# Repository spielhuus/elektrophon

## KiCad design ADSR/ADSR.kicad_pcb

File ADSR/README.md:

# The Fastest Envelope in the West

The ADSR creates an envelope for describing the change of the sound over time. The envelope can be used for amplitude, 
<a href="https://spielhuus.github.io/elektrophon/images/ADSR_panel.png"></img></a>
frequencies or pitch. The output of the ADSR module can for example be patched to a VCA or VCF. The original schematic is
used by René Schmitz and Yves Usson. 
<a href="https://spielhuus.github.io/elektrophon/images/ADSR.svg"></img></a>

<a href="https://spielhuus.github.io/elektrophon/images/ADSR.png"></img></a>

## links

1) [Wikipedia: ADSR](https://en.wikipedia.org/wiki/Envelope_(music))
1) [René Schmitz: The Fastest Envelope in the West](https://www.schmitzbits.de/adsr.html)
1) [Yves Usson: ADSR](http://www.yusynth.net/Modular/EN/ADSR/index_old.html)
1) [Falstad: Circuit simulation](https://www.falstad.com/circuit/circuitjs.html?cct=$+1+0.000005+382.76258214399064+66+5+43%0A165+288+80+384+80+6+1.7128468214015743e-7%0Ag+-192+208+-192+240+0%0AR+352+48+352+0+0+0+40+15+0+0+0.5%0At+-160+144+-128+144+0+1+-12.879237515528416+-0.40832239409727095+100%0Ar+-224+144+-288+144+0+10000%0Ad+-192+208+-192+144+2+default%0Ag+384+240+384+272+0%0Aw+-224+144+-192+144+0%0Aw+-192+144+-160+144+0%0Ar+-128+128+-128+64+0+4700%0Ar+-32+112+-32+48+0+4700%0At+-64+160+-32+160+0+1+0.5774361071439447+0.6326454792662959+100%0Ar+96+160+96+96+0+4700%0At+64+176+96+176+0+1+-14.984006479709088+0.015993518948659767+100%0AR+-128+64+-128+16+0+0+40+15+0+0+0.5%0AR+-32+48+-32+0+0+0+40+15+0+0+0.5%0AR+96+96+96+48+0+0+40+15+0+0+0.5%0Ar+-64+128+-128+128+0+22000%0Ad+16+208+16+144+2+default%0Ag+16+208+16+240+0%0Ar+64+144+16+144+0+10000%0Ac+-32+144+16+144+0+1e-8+0.039215854165133346%0Ag+96+192+96+240+0%0Ac+352+272+352+240+0+1e-8+-10.000000000000005%0Ag+352+272+352+320+0%0Aw+96+160+288+176+0%0AR+-288+144+-336+144+0+2+5+5+0+0+0.4%0Aa+592+192+688+192+8+15+-15+1000000+0.4192033211698532+0.4192075132030649+100000%0Aw+592+176+592+128+0%0Aw+592+128+688+128+0%0Aw+688+128+688+192+0%0Ap+752+192+832+192+1+0%0Ac+592+288+592+208+0+0.0000022+-0.4192075132030649%0Ag+592+288+592+320+0%0Ad+464+144+528+144+2+default%0Aw+528+144+528+208+0%0Aw+528+208+592+208+0%0A174+432+32+496+64+1+1000000+0.005+release%0Ad+528+112+480+112+2+default%0Aw+528+112+528+144+0%0Aw+288+208+528+208+0%0Aa+288+416+384+416+8+15+-15+1000000+3.8973097692544485+3.8973487423521407+100000%0Aw+288+112+192+112+0%0Aw+192+112+192+400+0%0A174+192+400+256+400+1+10000+0.38120000000000004+Sustain%0Aw+224+384+288+432+0%0Aw+288+400+288+368+0%0Aw+288+368+384+368+0%0Aw+384+368+384+416+0%0AR+256+336+256+288+0+0+40+15+0+0+0.5%0Ar+256+400+256+336+0+4700%0A174+384+416+448+416+1+1000000+0.024800000000000003+Decay%0Aw+416+400+512+320+0%0Ad+528+208+512+288+2+default%0Ar+416+48+416+112+0+100%0Ar+416+144+416+176+0+100%0Aw+432+32+416+32+0%0Aw+416+32+416+48+0%0Aw+464+64+464+112+0%0Aw+464+112+480+112+0%0A174+416+176+512+144+1+1000000+0.32180000000000003+Attack%0Ar+512+288+512+320+0+100%0Aw+-64+128+-64+160+0%0Ag+-128+160+-128+208+0%0Aw+64+144+64+176+0%0Ag+-32+176+-32+224+0%0Aw+-32+144+-32+112+0%0Aw+416+112+288+80+0%0Aw+288+80+-32+112+0%0Ar+688+192+752+192+0+1000%0Ao+26+64+0+4099+5+0.00078125+0+2+26+3%0Ao+31+64+0+4098+20+0.1+1+1%0A)
---

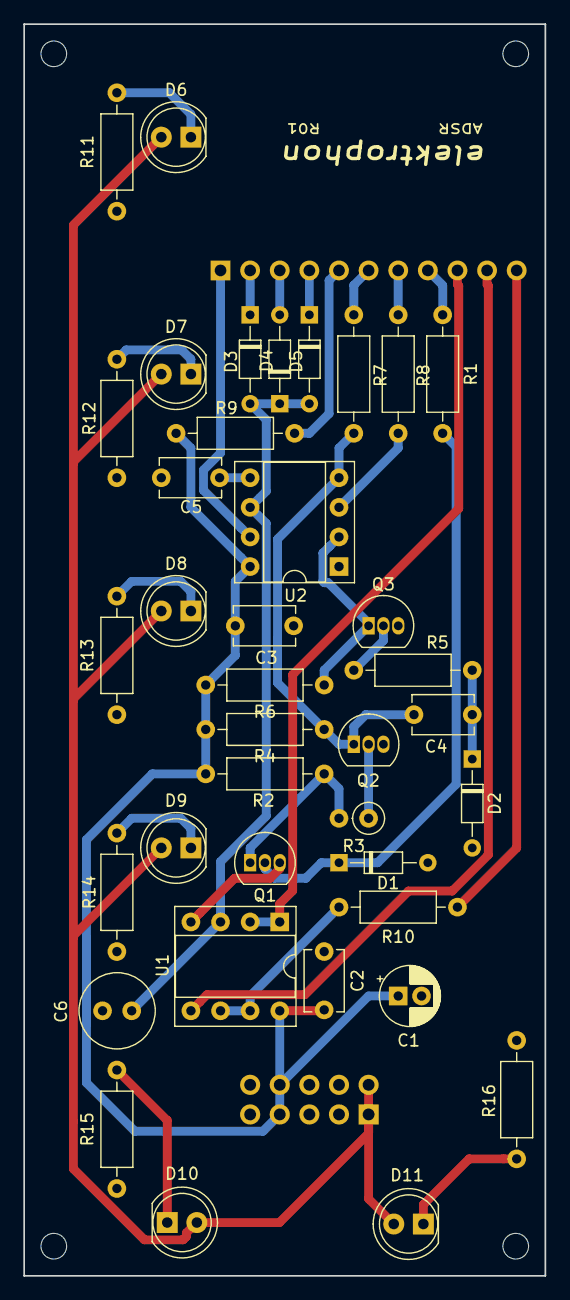
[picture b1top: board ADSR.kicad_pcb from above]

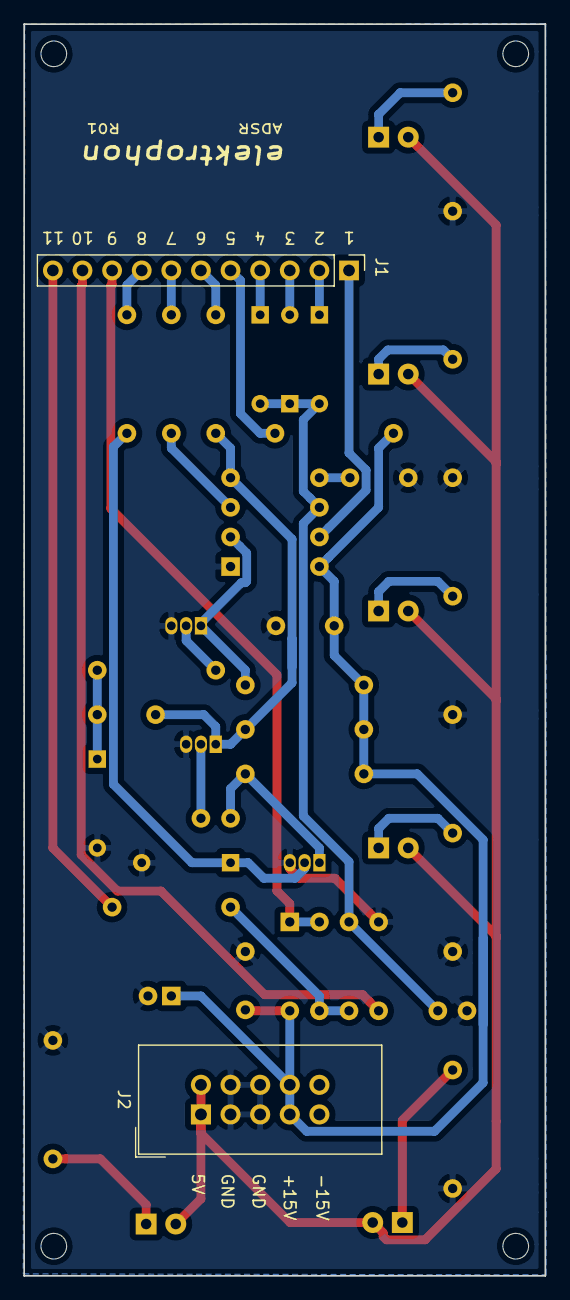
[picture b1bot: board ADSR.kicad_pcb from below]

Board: 2 copper layers, 44.7 x 107.3 mm, 40 parts (2 on the bottom side), 31 nets.

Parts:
C1: 22u; CP_Radial_D5.0mm_P2.00mm
C2, C3: 0.1u; C_Disc_D5.1mm_W3.2mm_P5.00mm
C4, C5: 10n; C_Disc_D5.1mm_W3.2mm_P5.00mm
C6: 4u7; C_Radial_D6.3mm_H5.0mm_P2.50mm
D1, D2, D3, D4, D5: D; D_DO-34_SOD68_P7.62mm_Horizontal
D6, D7, D8, D9, D10, D11: LED; LED_D5.0mm_FlatTop
J1: Panel; PinHeader_1x11_P2.54mm_Vertical
J2: Power; IDC-Header_2x05_P2.54mm_Vertical
Q1, Q2, Q3: BC547; TO-92_Inline
R1, R5: 10k; R_Axial_DIN0207_L6.3mm_D2.5mm_P10.16mm_Horizontal
R2, R4, R6, R9: 4k7; R_Axial_DIN0207_L6.3mm_D2.5mm_P10.16mm_Horizontal
R3: 22k; R_Axial_DIN0207_L6.3mm_D2.5mm_P2.54mm_Vertical
R7, R8, R10: 100; R_Axial_DIN0207_L6.3mm_D2.5mm_P10.16mm_Horizontal
R11, R12, R13, R14, R15, R16: 150; R_Axial_DIN0207_L6.3mm_D2.5mm_P10.16mm_Horizontal
U1: LM358; DIP-8_W7.62mm_Socket
U2: ICM7555; DIP-8_W7.62mm_Socket

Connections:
+5V: D6.2, D7.2, D8.2, D9.2, D10.2, D11.2, J2.1, J2.2
+15V: C1.1, C2.2, C3.1, J2.7, J2.8, R2.1, R4.1, R6.1, R9.2, U1.8, U2.8
Attack_1: J1.7, R8.1
Attack_2: D4.2, J1.3
Decay_1: D5.1, J1.4
Decay_2: J1.11, R10.2
GND: C1.2, C2.1, C3.2, C5.1, C6.2, D1.2, D2.2, J2.3, J2.4, J2.5, J2.6, Q1.3, Q2.3, Q3.3, R11.2, R12.1, R13.2, R14.1, R15.2, R16.1, U1.4, U2.1
IN: J1.8, R1.2
unnamed: C4.1, D2.1, R5.2
unnamed: C4.2, Q2.1, R4.2, R7.2, U2.4
unnamed: C5.2, U2.5
unnamed: C6.1, D3.2, D4.1, D5.2, U1.3, U2.6
unnamed: D1.1, Q1.2, R1.1
unnamed: D6.1, R11.1
unnamed: D7.1, R12.2
unnamed: D8.1, R13.1
unnamed: D9.1, R14.2
unnamed: D10.1, R15.1
unnamed: D11.1, R16.2
unnamed: Q1.1, R2.2, R3.2
unnamed: Q2.2, R3.1
unnamed: Q3.1, R6.2, U2.2
unnamed: Q3.2, R5.1
unnamed: R8.2, U2.3
unnamed: R10.1, U1.6, U1.7
OUT: J1.9, U1.1, U1.2
Release_1: J1.6, R7.1
Release_2: D3.1, J1.2
Sustain_1: J1.5, R9.1
Sustain_2: J1.10, U1.5
Sustain_3: J1.1, U2.7

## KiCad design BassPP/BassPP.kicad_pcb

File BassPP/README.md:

# Bass++

This is a basic VCO designed by Thomas Henry. There are no special features, but it is a solid mixer.

Lorem ipsum dolor sit amet, consectetuer adipiscing elit. Aenean commodo ligula eget dolor. Aenean massa. Cum sociis natoque
penatibus et magnis dis parturient montes, nascetur ridiculus mus. Donec quam felis, ultricies nec, pellentesque eu, pretium quis, sem. Nulla consequat massa quis enim. Donec pede justo, fringilla vel, aliquet nec, vulputate eget, arcu. In enim justo, rhoncus ut, imperdiet a, venenatis vitae, justo. Nullam dictum felis eu pede mollis pretium. Integer tincidunt. Cras dapibus. Vivamus elementum semper nisi. Aenean vulputate eleifend tellus. Aenean leo ligula, porttitor eu, consequat vitae, eleifend ac, enim. Aliquam lorem ante, dapibus in, viverra quis, feugiat a, tellus. Phasellus viverra nulla ut metus varius laoreet. Quisque rutrum. Aenean imperdiet. Etiam ultricies nisi vel augue. Curabitur ullamcorper ultricies nisi. Nam eget dui. Etiam rhoncus. Maecenas tempus, tellus eget condimentum rhoncus, sem quam semper libero, sit amet adipiscing sem neque 

sed ipsum. Nam quam nunc, blandit vel, luctus pulvinar, hendrerit id, lorem. Maecenas nec odio et ante tincidunt tempus. Donec vitae sapien ut libero venenatis faucibus. Nullam quis ante. Etiam sit amet orci eget eros faucibus tincidunt. Duis leo. Sed fringilla mauris sit amet nibh. Donec sodales sagittis magna. Sed consequat, leo eget bibendum sodales, augue velit cursus nunc, Lorem ipsum dolor sit amet, consectetuer adipiscing elit. Aenean commodo ligula eget dolor. Aenean massa. Cum sociis natoque penatibus et magnis dis parturient montes, nascetur ridiculus mus. Donec quam felis, ultricies nec, pellentesque eu, pretium quis, sem. Nulla consequat massa quis enim. Donec pede justo, fringilla vel, aliquet nec, vulputate eget, arcu. In enim justo, rhoncus ut, imperdiet a, venenatis vitae, justo. Nullam dictum felis eu pede mollis pretium. Integer tincidunt. Cras dapibus. Vivamus elementum semper nisi. Aenean vulputate eleifend tellus. Aenean leo ligula, porttitor eu, consequat vitae, eleifend ac, enim. Aliquam lorem ante, dapibus in, viverra quis, feugiat a, tellus. Phasellus viverra nulla ut metus varius laoreet. Quisque rutrum. Aenean imperdiet. Etiam ultricies nisi vel augue. 

Curabitur ullamcorper ultricies nisi. Nam eget dui. Etiam rhoncus. Maecenas tempus, tellus eget condimentum rhoncus, sem quam semper libero, sit amet adipiscing sem neque sed ipsum. Nam quam nunc, blandit vel, luctus pulvinar, hendrerit id, lorem. Maecenas nec odio et ante tincidunt tempus. Donec vitae sapien ut libero venenatis faucibus. Nullam quis ante. Etiam sit amet orci eget eros faucibus tincidunt. Duis leo. Sed fringilla mauris sit amet nibh. Donec sodales sagittis magna. Sed consequat, leo eget bibendum sodales, augue velit cursus nunc - [BOM](BOM.csv) adipiscing sem neque sed ipsum. Nam quam nunc, blandit vel, luctus pulvinar, hendrerit id, lorem. Maecenas nec odio et ante tincidunt tempus. Donec vitae sapien ut libero venenatis faucibus. Nullam quis ante. Etiam sit amet orci eget eros faucibus tincidunt. Duis leo. Sed fringilla mauris sit amet nibh. Donec sodales sagittis magna. Sed consequat, leo eget bibendum sodales, augue velit cursus nun

## links

1) [Thomas Henry: Bass++]()

---

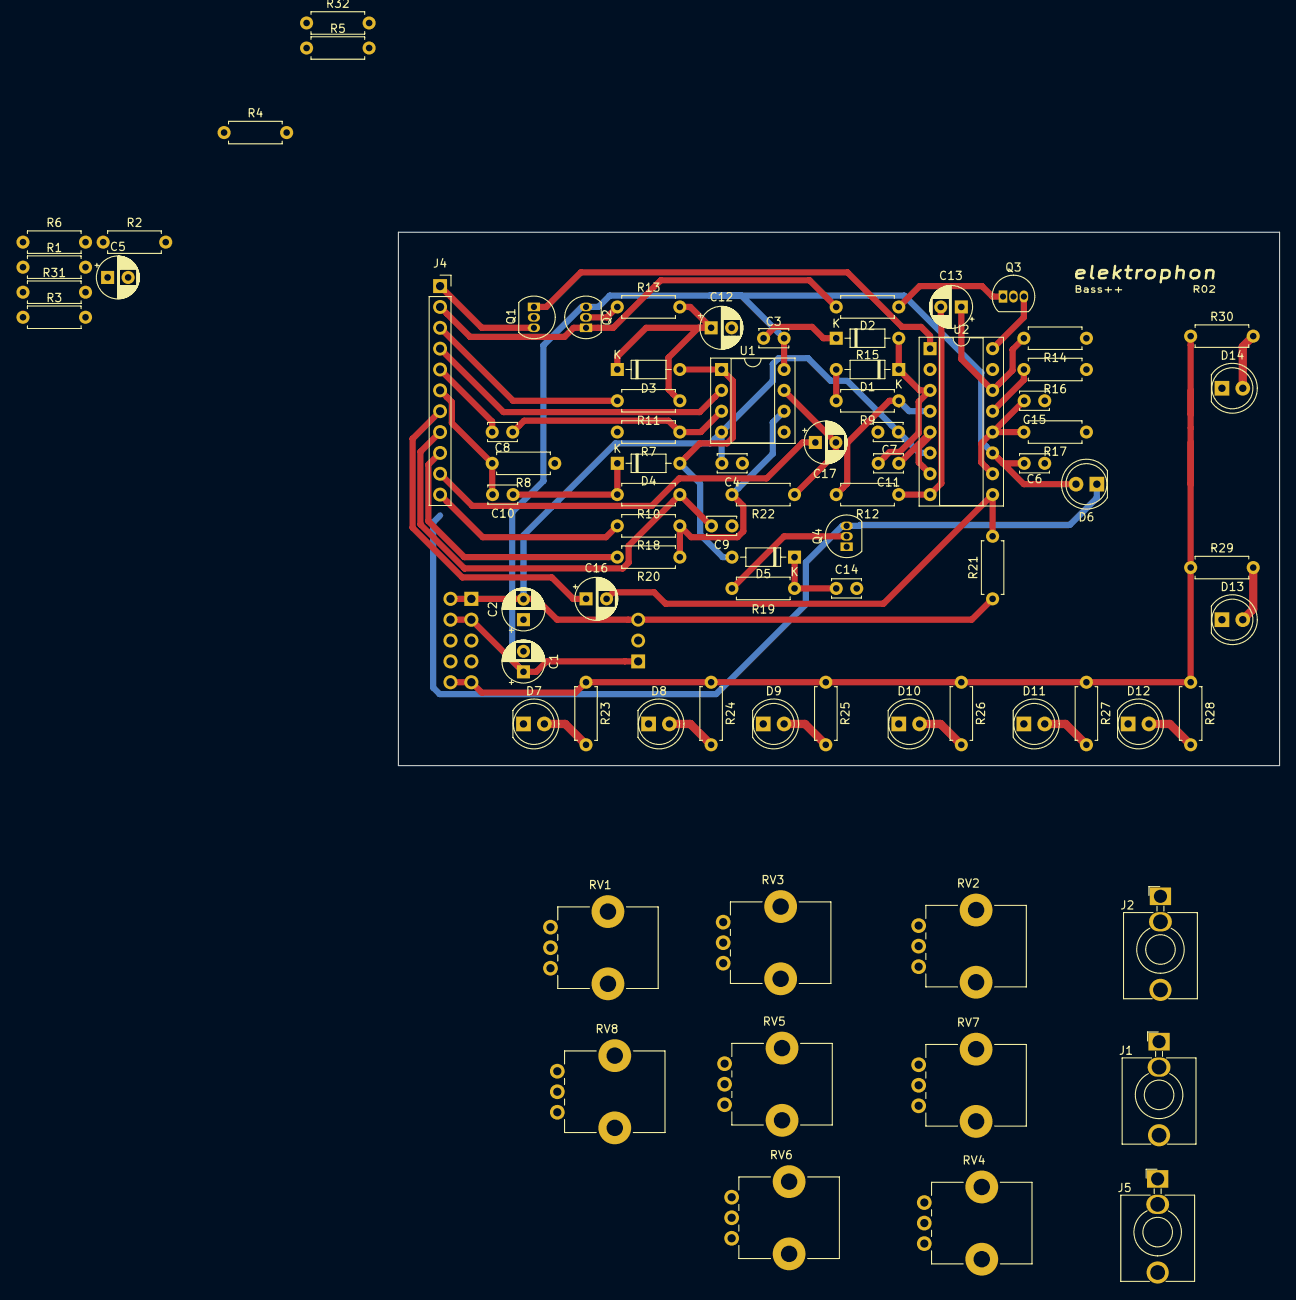
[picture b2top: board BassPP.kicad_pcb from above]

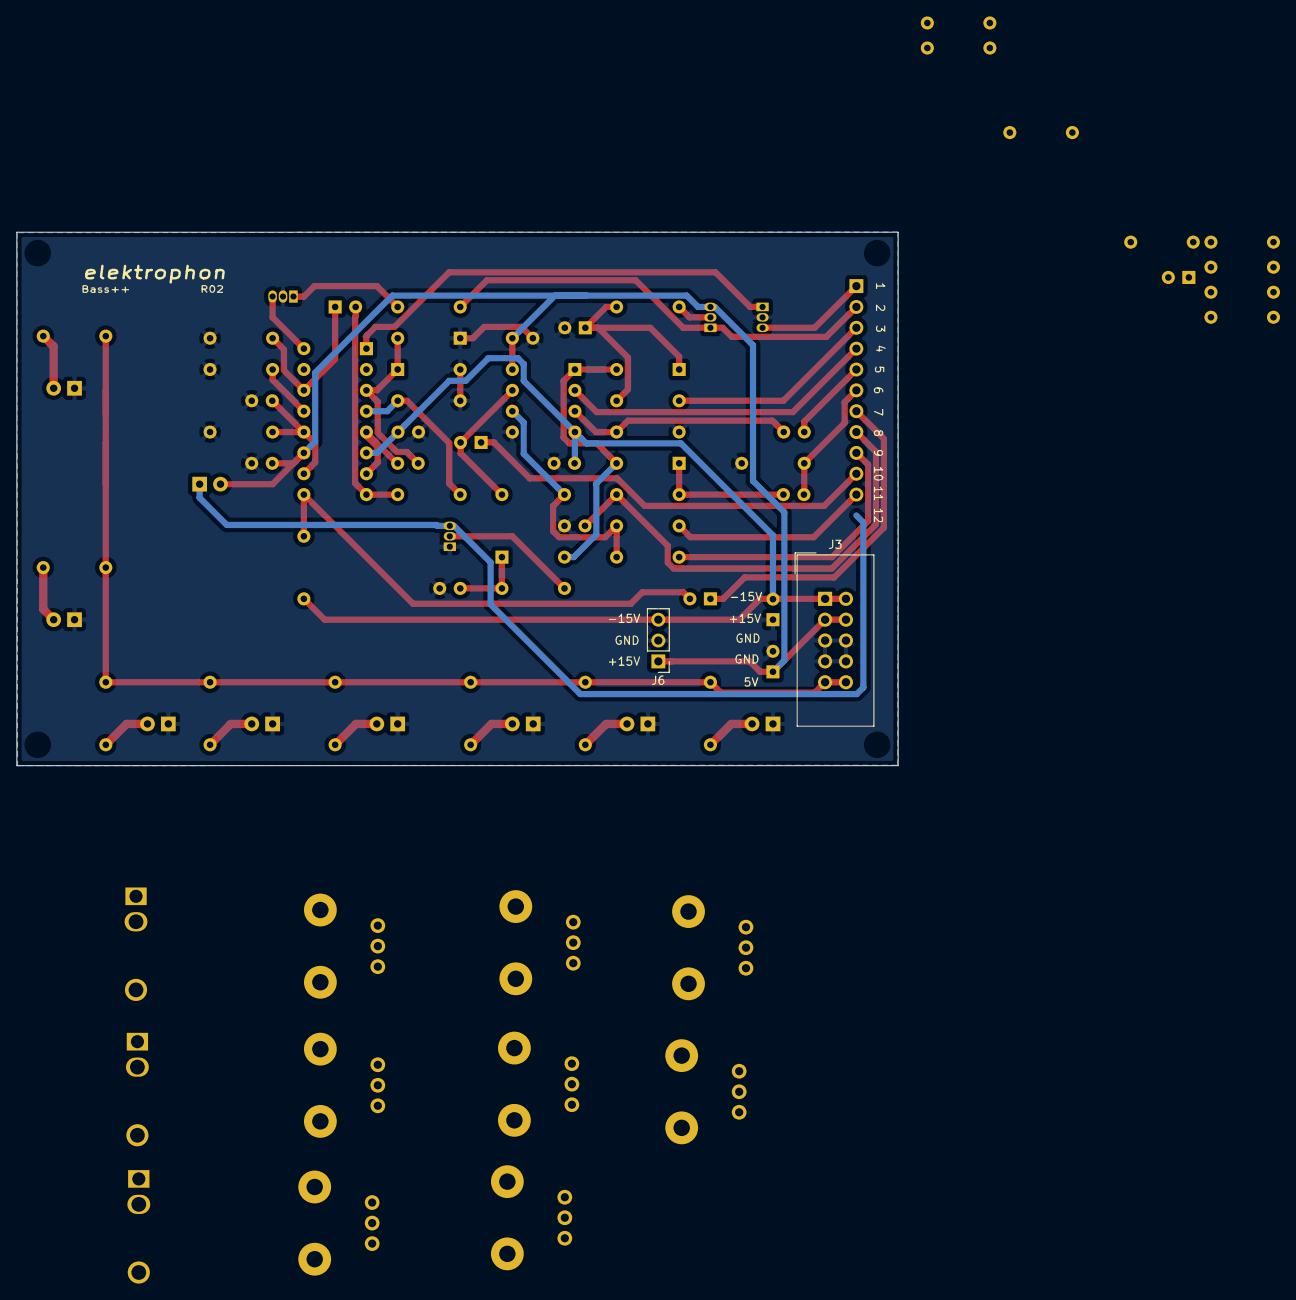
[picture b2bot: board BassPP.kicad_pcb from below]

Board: 2 copper layers, 107.3 x 65.0 mm, 83 parts (2 on the bottom side), 53 nets.

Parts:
C1, C2: 10u; CP_Radial_D5.0mm_P2.50mm
C3, C4, C6, C7, C9, C10: 0.1u; C_Disc_D3.4mm_W2.1mm_P2.50mm
C5, C12, C13, C16, C17: 2u2; CP_Radial_D5.0mm_P2.50mm
C8: 1n; C_Disc_D3.4mm_W2.1mm_P2.50mm
C11: 4n7; C_Disc_D3.4mm_W2.1mm_P2.50mm
C14, C15: 10n; C_Disc_D3.4mm_W2.1mm_P2.50mm
D1, D2, D3, D4, D5: 1N4148; D_DO-35_SOD27_P7.62mm_Horizontal
D6, D7, D8, D9, D10, D11, D12, D13, D14: LED; LED_D5.0mm_FlatTop
J1, J2, J5: AudioJack3_Ground; Jack_3.5mm_QingPu_WQP-PJ398SM_Vertical_CircularHoles
J3: IDC Header; IDC-Header_2x05_P2.54mm_Vertical
J4: Pin Header; PinSocket_1x11_P2.54mm_Vertical
J6: Pin Header; PinHeader_1x03_P2.54mm_Vertical
Q1, Q3: 2N3906; TO-92_Inline
Q2, Q4: 2N3904; TO-92_Inline
R1: 100; R_Axial_DIN0207_L6.3mm_D2.5mm_P7.62mm_Horizontal
R2, R12, R15: 20k; R_Axial_DIN0207_L6.3mm_D2.5mm_P7.62mm_Horizontal
R3, R18, R20, R22, R32: 100k; R_Axial_DIN0207_L6.3mm_D2.5mm_P7.62mm_Horizontal
R4, R17: 56k; R_Axial_DIN0207_L6.3mm_D2.5mm_P7.62mm_Horizontal
R5: 27k; R_Axial_DIN0207_L6.3mm_D2.5mm_P7.62mm_Horizontal
R6: 3k3; R_Axial_DIN0207_L6.3mm_D2.5mm_P7.62mm_Horizontal
R7: 1M; R_Axial_DIN0207_L6.3mm_D2.5mm_P7.62mm_Horizontal
R8, R9: 2k; R_Axial_DIN0207_L6.3mm_D2.5mm_P7.62mm_Horizontal
R10, R13, R21: 10k; R_Axial_DIN0207_L6.3mm_D2.5mm_P7.62mm_Horizontal
R11: 1k; R_Axial_DIN0207_L6.3mm_D2.5mm_P7.62mm_Horizontal
R14, R16: 220; R_Axial_DIN0207_L6.3mm_D2.5mm_P7.62mm_Horizontal
R19, R23, R24, R25, R26, R27, R28, R29, R30: 220k; R_Axial_DIN0207_L6.3mm_D2.5mm_P7.62mm_Horizontal
R31: 5k1; R_Axial_DIN0207_L6.3mm_D2.5mm_P7.62mm_Horizontal
RV1, RV3, RV8: 10k; Potentiometer_Bourns_PTV09A-1_Single_Vertical
RV2: 500k; Potentiometer_Bourns_PTV09A-1_Single_Vertical
RV4, RV5, RV6, RV7: 100k; Potentiometer_Bourns_PTV09A-1_Single_Vertical
U1: TL072; DIP-8_W7.62mm_Socket
U2: LM13700; DIP-16_W7.62mm_Socket

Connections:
+5V: J3.9, J3.10, R23.1, R24.1, R25.1, R26.1, R27.1, R28.1, R29.1, R30.1
+15V: C1.1, C3.1, C6.1, D6.2, J3.3, J3.4, J6.1, Q2.3, R2.1, RV5.1, U1.8, U2.11
-15V: C2.2, C4.2, C7.2, J3.1, J3.2, J6.3, R21.1, R31.1, U1.4, U2.6
/CV1: J4.2, Q2.1, R15.2, RV3.1
/CV2: J4.1, Q1.1, R3.1, R4.1, R5.1
/DECAY: J4.3, R11.1, RV2.2
/ImpactTone: J4.9, R20.2, RV8.2
/ImpactVolume1: C10.2, J4.6, R8.2, RV7.1
/ImpactVolume2: C9.2, J4.8, R10.1, RV7.3
/OUT: C17.1, J4.10
/PULSE: D3.2, D4.2, D5.2, U1.1
/SENSITIVITY: J4.4, RV1.2, U1.2
/Shell: C16.1, J4.7, RV6.1
/ShellVolume: J4.11, R18.2, RV6.2
/TRIGGER: C8.1, J4.5
GND: C1.2, C2.1, C3.2, C4.1, C6.2, C7.1, C9.1, C12.2, C14.2, C15.1, D1.2, D2.1, D7.1, D8.1, D9.1, D10.1, D11.1, D12.1, D13.1, D14.1, J3.5, J3.6, J3.7, J3.8, J6.2, Q1.2, Q3.2, Q4.1, R1.1, R6.1, R7.1, R8.1, R9.2, R14.1, R16.1, R17.1, RV2.3, RV3.3, RV4.3, RV6.3, RV8.3, U1.5
unnamed: C5.1, RV8.1
unnamed: C5.2, RV7.2
unnamed: C8.2, R7.2, U1.3
unnamed: C10.1, D4.1, R10.2
unnamed: C11.1, U2.5, U2.7
unnamed: C11.2, D1.1, D2.2, U2.3
unnamed: C12.1, D3.1, R11.2, R13.2
unnamed: C13.1, R32.1
unnamed: C13.2, R12.1, R31.2, U2.8
unnamed: C14.1, D5.1, R19.2
unnamed: C15.2, R17.2, U2.10, U2.12
unnamed: C16.2, R21.2, U2.9
unnamed: C17.2, R22.1, U1.7
unnamed: D6.1, Q4.3
unnamed: D7.2, R23.2
unnamed: D8.2, R24.2
unnamed: D9.2, R25.2
unnamed: D10.2, R26.2
unnamed: D11.2, R27.2
unnamed: D12.2, R28.2
unnamed: D13.2, R29.2
unnamed: D14.2, R30.2
unnamed: Q1.3, U2.1
unnamed: Q2.2, R13.1
unnamed: Q3.1, R15.1
unnamed: Q3.3, U2.16
unnamed: Q4.2, R19.1
unnamed: R1.2, RV1.1
unnamed: R2.2, RV1.3
unnamed: R3.2, RV3.2
unnamed: R4.2, RV4.2
unnamed: R5.2, RV5.2
unnamed: R6.2, RV5.3
unnamed: R9.1, R12.2, U2.4
unnamed: R14.2, R32.2, U2.14
unnamed: R16.2, U2.13
unnamed: R18.1, R20.1, R22.2, U1.6

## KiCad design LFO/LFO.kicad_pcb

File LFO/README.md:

# LFO

<a href="https://spielhuus.github.io/elektrophon/lfo_schema._panel.jpg"></img></a>
<a href="https://spielhuus.github.io/elektrophon/lfo_panel_back.jpg"></img></a>
<a href="https://spielhuus.github.io/elektrophon/lfo_schema.svg"></img></a>
<a href="https://spielhuus.github.io/elektrophon/lfo_stripboard.png"></img></a>

Simple but fancy LFO from Ken Stone. It is a dual LFO with pulse, square, triangle/saw and vari output. the vari output is a mixture of the square and triangle output. the two vari output can be combined with the switch. 

## BOM

|Ref|Value|Name|
|:---|:---|:---|
|C1|22u|Ceramic Capacitor|

## links

1) [CGS58: Utility LFO](http://www.elby-designs.com/webtek/cgs/cgs58/cgs58_lfo.html)
2) [falstad circuit simulation](https://www.falstad.com/circuit/circuitjs.html?cct=$+1+0.000005+7.010541234668786+50+5+43%0Ag+-384+256+-384+320+0%0Ar+-384+160+-272+160+0+200000%0Aa+-384+240+-272+240+9+15+-15+1000000+0+-0.4042806600601523+100000%0Aw+-384+160+-384+224+0%0Aw+-272+160+-272+240+0%0Ad+-144+192+-32+192+2+default%0Ad+-32+288+-144+288+2+default%0Aw+-16+240+32+240+0%0Aa+112+256+192+256+8+15+-15+1000000+-0.00006893599216459132+0+100000%0Ar+32+240+112+240+0+10000%0Ac+96+176+192+176+0+4.7000000000000004e-8+-6.893668152451296%0Aw+96+176+112+240+0%0Aw+192+176+192+256+0%0Ar+-384+64+192+64+0+100000%0Aw+192+64+192+176+0%0Ap+192+320+144+320+1+0%0Ap+-272+320+-320+320+1+0%0Aa+448+256+576+256+8+15+-15+1000000+10.204448530291327+10.20455057477663+100000%0Ar+368+272+448+272+0+47000%0Ap+576+320+624+320+1+0%0Aw+448+240+448+176+0%0Aw+448+176+576+176+0%0Aw+576+176+576+256+0%0Ag+272+288+272+336+0%0Ap+848+128+944+128+1+0%0A174+-208+240+-208+320+0+100000+0.19310000000000002+Speed%0A174+-32+192+-32+272+0+100000+0.005+Shape%0Ag+112+272+112+320+0%0Aa+272+272+368+272+9+15+-15+1000000+0+6.893599216459132+100000%0Ar+192+256+272+256+0+100000%0Aw+192+64+576+64+0%0Ar+448+272+448+352+0+100000%0Ag+448+352+448+368+0%0Aw+-272+240+-208+240+0%0Aw+-384+64+-384+160+0%0A174+576+64+576+160+0+100000+0.3713+Resistance%0Ar+-272+240+-272+320+0+2200%0Ar+-272+320+-272+400+0+1000%0Ar+192+256+192+320+0+1000%0Ar+192+320+192+384+0+1000%0Ar+576+256+576+320+0+1000%0Ar+576+320+576+400+0+1000%0Ag+576+400+576+432+0%0Ag+192+384+192+416+0%0Ag+-272+400+-272+448+0%0Ar+768+128+848+128+0+1000%0Aa+656+128+768+128+9+15+-15+1000000+8.12283633832164+8.122917566685024+100000%0Aw+592+112+656+112+0%0Aw+656+144+656+208+0%0Aw+656+208+768+208+0%0Aw+768+208+768+128+0%0Ar+-208+336+-208+400+0+4700%0Ag+-208+400+-208+448+0%0Aw+-144+192+-144+288+0%0Aw+-144+288+-192+288+0%0Aw+576+160+576+176+0%0A403+896+176+1024+240+0+24_64_0_4098_10_0.1_0_1%0A403+624+368+752+432+0+19_64_0_4098_10_0.1_0_1%0A403+240+368+368+432+0+15_64_0_4098_5_0.1_0_1%0A403+-224+368+-96+432+0+16_64_0_4098_5_0.1_0_1%0A)

---

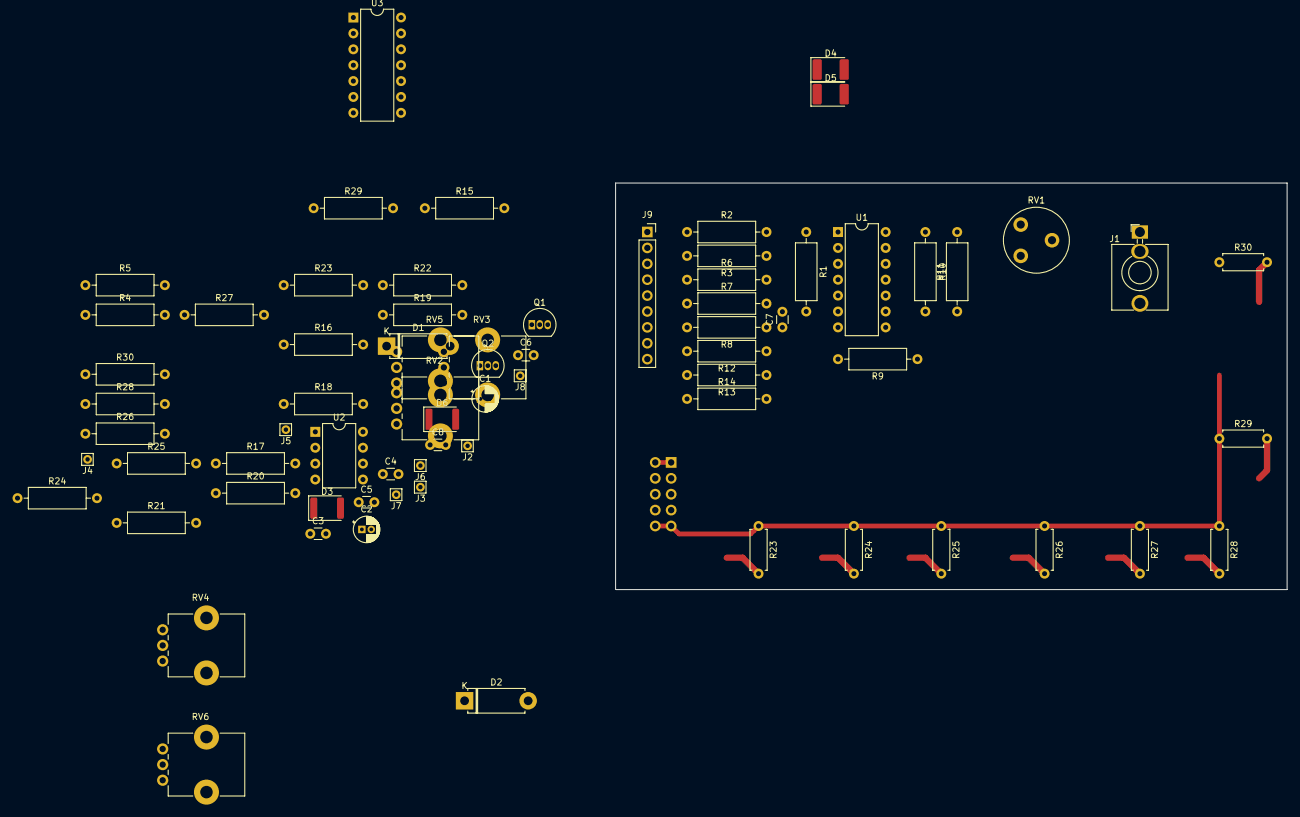
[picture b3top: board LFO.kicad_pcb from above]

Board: 2 copper layers, 107.3 x 65.0 mm, 73 parts (1 on the bottom side), 46 nets.

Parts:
C1, C2: CP; CP_Radial_D4.0mm_P1.50mm
C3, C4, C5, C6: 100n; C_Disc_D3.0mm_W1.6mm_P2.50mm
C7, C8: 47n; C_Disc_D3.0mm_W1.6mm_P2.50mm
D1, D2: D; D_5W_P10.16mm_Horizontal
D3, D6: LED; LED_1812_4532Metric
D4, D5: D; D_1812_4532Metric_Castellated
J1: AudioJack3; Jack_3.5mm_QingPu_WQP-PJ398SM_Vertical_CircularHoles
J2, J6: TRI/SAW; Pin_D0.7mm_L6.5mm_W1.8mm_FlatFork
J3, J7: Square; Pin_D0.7mm_L6.5mm_W1.8mm_FlatFork
J3#2: POWER; IDC-Header_2x05_P2.54mm_Vertical
J4, J8: VARI; Pin_D0.7mm_L6.5mm_W1.8mm_FlatFork
J5: PULSE; Pin_D0.7mm_L6.5mm_W1.8mm_FlatFork
J9: Conn_01x09_Male; PinSocket_1x09_P2.54mm_Vertical
Q1, Q2: BC547; TO-92_Inline
R1, R16: 150k; R_Axial_DIN0309_L9.0mm_D3.2mm_P12.70mm_Horizontal
R2, R17: 2k2; R_Axial_DIN0309_L9.0mm_D3.2mm_P12.70mm_Horizontal
R3, R7, R8, R12, R13, R14, R15, R18, R22, R23, R27, R28, R29, R30: 1k; R_Axial_DIN0309_L9.0mm_D3.2mm_P12.70mm_Horizontal
R4, R19: 4k7; R_Axial_DIN0309_L9.0mm_D3.2mm_P12.70mm_Horizontal
R5, R9, R11, R20, R24, R26: 100k; R_Axial_DIN0309_L9.0mm_D3.2mm_P12.70mm_Horizontal
R6, R21: 10k; R_Axial_DIN0309_L9.0mm_D3.2mm_P12.70mm_Horizontal
R10, R25: 47k; R_Axial_DIN0309_L9.0mm_D3.2mm_P12.70mm_Horizontal
R23#2, R24#2, R25#2, R26#2, R27#2, R28#2, R29#2, R30#2: 220k; R_Axial_DIN0207_L6.3mm_D2.5mm_P7.62mm_Horizontal
RV1: 100k; Potentiometer_Piher_PT-10-V05_Vertical
RV2, RV5: 500k; Potentiometer_Alps_RK09K_Single_Vertical
RV3, RV4, RV6: 100k; Potentiometer_Alps_RK09K_Single_Vertical
U1, U3: TL074; DIP-14_W7.62mm
U2: TL072; DIP-8_W7.62mm

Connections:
+5V: J3#2.9, J3#2.10, R23#2.1, R24#2.1, R25#2.1, R26#2.1, R27#2.1, R28#2.1, R29#2.1, R30#2.1
+15V: C1.1, C3.2, C5.2, J3#2.3, J3#2.4, Q1.1, Q2.1, U1.4, U2.8
-15V: C2.2, C4.1, C6.1, J3#2.1, J3#2.2, U1.11, U2.4
/PULSE: J5.1, R17.1, R18.2
/PULSE_A: J1.S, J9.1, R2.1, R3.2
/SPEED_1: R16.1, R17.2, RV4.1, U3.1
/SPEED_1_A: J9.2, R1.1, R2.2, RV1.1, U1.1
/SPEED_2: R21.1, RV5.2
/SPEED_2_A: J9.3, R6.1, RV2.2
/Square: J3.1, J9.5, R12.1, R13.2
/Square_1_A: J9.6, R12.2, RV3.1, U1.13, U1.14
/Square_2_A: J9.7, RV3.2, U2.3
/Square_3_A: C7.1, J9.8, Q1.2, R5.1, R7.2, R9.2, RV3.3, U1.7
/TRI_SAW_A: J2.1, J9.4, R7.1, R8.2
/VARI: J4.1, J9.9, R14.1
GND: C1.2, C2.1, C3.1, C4.2, C5.1, C6.2, D3.1, D6.1, J1.T, J3#2.5, J3#2.6, J3#2.7, J3#2.8, R3.1, R4.2, R8.1, R11.1, R13.1, R18.1, R19.2, R23.1, R26.1, R28.1, U1.2, U1.5, U1.9, U3.2, U3.5, U3.9
unnamed: C7.2, R6.2, U1.6
unnamed: C8.1, Q2.2, R20.1, R22.2, R24.2, RV6.3, U3.7
unnamed: C8.2, R21.2, U3.6
unnamed: D1.1, D2.2, RV1.2
unnamed: D1.2, RV2.3
unnamed: D2.1, RV2.1
unnamed: D3.2, R15.1
unnamed: D4.1, D5.2, RV4.2
unnamed: D4.2, RV5.3
unnamed: D5.1, RV5.1
unnamed: D6.2, R30.1
unnamed: J6.1, R22.1, R23.2
unnamed: J7.1, R27.1, R28.2
unnamed: J8.1, R29.1
unnamed: Q1.3, R15.2
unnamed: Q2.3, R30.2
unnamed: R1.2, R5.2, U1.3
unnamed: R4.1, RV1.3
unnamed: R9.1, U1.10
unnamed: R10.1, R11.2, U1.12
unnamed: R10.2, U1.8
unnamed: R14.2, U2.1, U2.2
unnamed: R16.2, R20.2, U3.3
unnamed: R19.1, RV4.3
unnamed: R24.1, U3.10
unnamed: R25.1, R26.2, U3.12
unnamed: R25.2, U3.8
unnamed: R27.2, RV6.1, U3.13, U3.14
unnamed: R29.2, U2.6, U2.7
unnamed: RV6.2, U2.5

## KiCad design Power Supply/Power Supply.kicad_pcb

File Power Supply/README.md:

# Wall Wart Power Supply

The power supply is one of the first thing to build. It is important to have a stable power and voltage when building modules. 5V and +-15V are creatued from two wall wart power supplies as power sources. The circuit for the split AC voltage is the MFOS[1] wall wart supply. For the 5V a simple voltage regulator circuit. The 3 voltages and ground are connected with IDC connectors and are wired with banana plugs on the panel.

<a href="https://spielhuus.github.io/elektrophon/power_supply_board.jpg"></img></a>
<a href="https://spielhuus.github.io/elektrophon/Power_Supply_schema.svg"></img></a>
<a href="https://spielhuus.github.io/elektrophon/power_supply_stripboard.png"></img></a>

Input:
* 15VAC
* 12VDC

Output:
* +-12V/1A 
* +5V/1.5A
* Common Ground 

# BOM

|Qty.|Ref| Value| Description|
|---|------|----------|----------|
|1|W1| 15VAC| Wall Wart Power Supply 15VAC/1A|
|1|W2| 12VDC| Wall Wart Power Supply 12VDC/1.5A|
|6|C1-C6| 3300uF| Electrolytic Capacitors (D10.0mm_P2.50mm_P5.00mm)|
|4|C7-C10| 1uF| Electrolytic Capacitors|
|1|C11| 0.33uF| Ceramic Capacitor|
|1|C12| 0.1uF| Ceramic Capacitor|
|6|D1-D6| 1N4004| Rectifiers|
|1|U1| [LM7815](https://www.st.com/resource/en/datasheet/l78.pdf)| Positive voltage regulator +15V (TO220) |
|1|U2| [LM7815](https://www.st.com/resource/en/datasheet/cd00000450.pdf)| Negative voltage regulator -12V (TO220) |
|1|U3| [L7805](https://www.st.com/resource/en/datasheet/l78.pdf)| Positive voltage regulator +5V (TO220)|
|5|R1-R5| 100| Resistors |
|5|D7-11| red| LED's 3mm |
|3| U1-U3| | Heat Sinks for the Regulators (TO220) |
|1| | 200x160mm| Stripboard |
| | <td colspan=2> Wire, Sockets, Plugs, LEDs and Resistors |

# links

* [Wall Wart Power Supply (+/-9V to +/-15V)](http://musicfromouterspace.com/analogsynth_new/WALLWARTSUPPLY/WALLWARTSUPPLY.php)
* [The A-100 system bus](http://www.doepfer.de/a100_man/a100t_e.htm)
* [MFOS Power supply stripboard  on electro-music.com](http://electro-music.com/forum/topic-35373.html)

---

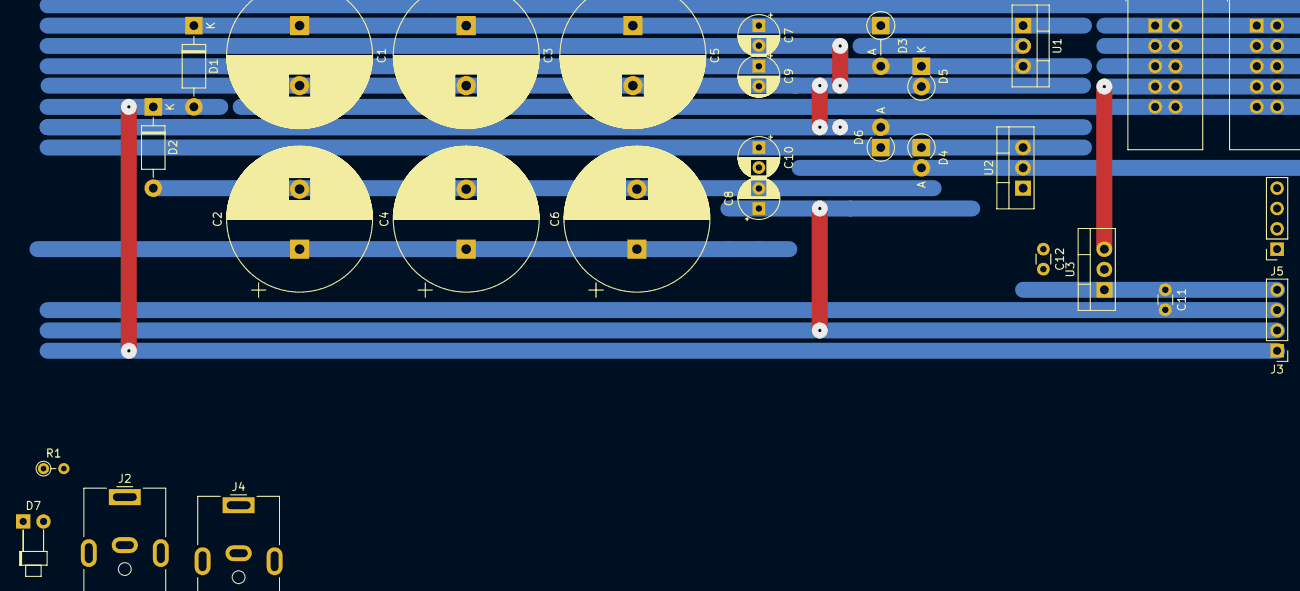
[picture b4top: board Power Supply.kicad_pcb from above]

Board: 2 copper layers, 29 parts (0 on the bottom side), 10 nets.

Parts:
C1, C2, C3, C4, C5, C6: 3300uF; CP_Radial_D18.0mm_P7.50mm
C7, C8, C9, C10: 1uF; CP_Radial_D5.0mm_P2.50mm
C11: 0.33; C_Disc_D3.0mm_W1.6mm_P2.50mm
C12: 0.1; C_Disc_D3.0mm_W1.6mm_P2.50mm
D1, D2: 1N4004; D_DO-41_SOD81_P10.16mm_Horizontal
D3: 1N4004; D_DO-41_SOD81_P5.08mm_Vertical_AnodeUp
D4, D6: 1N4004; D_DO-41_SOD81_P2.54mm_Vertical_AnodeUp
D5: 1N4004; D_DO-41_SOD81_P2.54mm_Vertical_KathodeUp
D7: LED; LED_D1.8mm_W1.8mm_H2.4mm_Horizontal_O3.81mm_Z1.6mm
J1, J6: Conn_02x05_Odd_Even; IDC-Header_2x05_P2.54mm_Vertical
J2, J4: Barrel_Jack; BarrelJack_CUI_PJ-063AH_Horizontal
J3: Power Input; PinHeader_1x04_P2.54mm_Vertical
J5: Conn_01x04_Male; PinSocket_1x04_P2.54mm_Vertical
R1: R; R_Axial_DIN0204_L3.6mm_D1.6mm_P2.54mm_Vertical
U1: L7815; TO-220-3_Vertical
U2: L7915; TO-220-3_Vertical
U3: L7805; TO-220-3_Vertical

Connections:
+5V: C12.1, D7.1, J1.7, J1.8, J5.4, J6.7, J6.8, U3.3
+12V: C11.1, J3.4, J4.1, U3.1
+15V: C9.1, D3.2, D5.1, J1.1, J1.2, J2.1, J5.1, J6.1, J6.2, U1.3
-15V: C10.2, D4.1, D6.2, J1.9, J1.10, J2.2, J5.2, J6.9, J6.10, U2.3
GND: C1.2, C2.1, C3.2, C4.1, C5.2, C6.1, C7.2, C8.1, C9.2, C10.1, D5.2, D6.1, J1.3, J1.4, J1.5, J1.6, J3.2, J3.3, J4.2, J5.3, J6.3, J6.4, J6.5, J6.6, R1.2, U1.2, U2.1, U3.2
unnamed: C1.1, C3.1, C5.1, C7.1, D1.1, D3.1, U1.1
unnamed: C2.2, C4.2, C6.2, C8.2, D2.2, D4.2, U2.2
unnamed: C11.2, C12.2
unnamed: D7.2, R1.1
VDDA: D1.2, D2.1, J3.1

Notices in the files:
ADSR/ADSR.kicad_pcb:
License CC BY 4.0 - Attribution 4.0 International
ADSR/README.md:
CC BY-SA
